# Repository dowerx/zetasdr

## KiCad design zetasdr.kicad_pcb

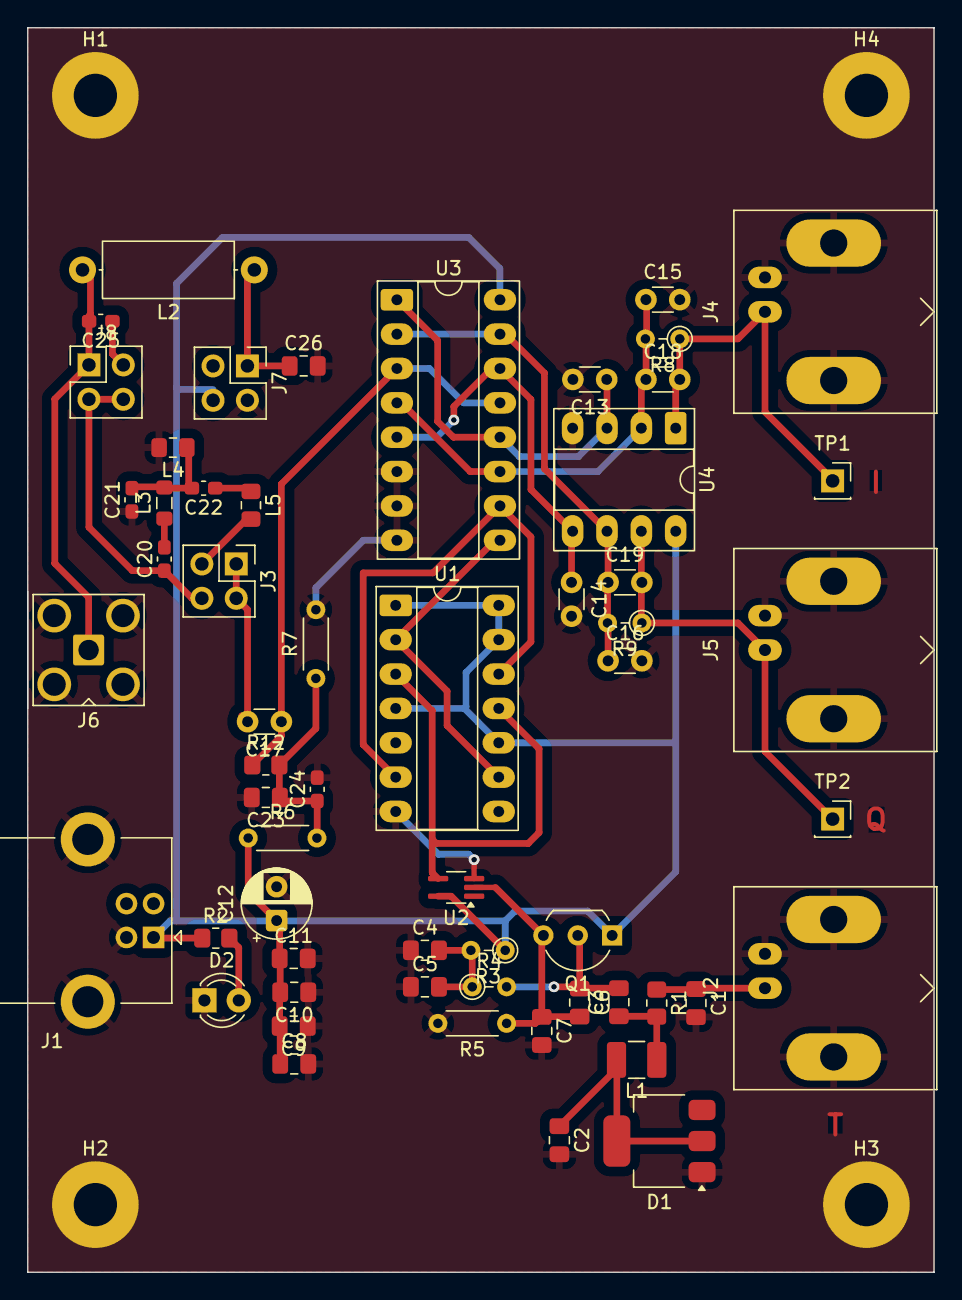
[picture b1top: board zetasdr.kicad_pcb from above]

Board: 2 copper layers, 67.0 x 92.0 mm, 62 parts (0 on the bottom side), 29 nets.

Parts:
C1, C3, C4, C8, C9, C10, C11, C23, C26: 100n; C_0805_2012Metric_Pad1.18x1.45mm_HandSolder
C2: DNP; C_0805_2012Metric_Pad1.18x1.45mm_HandSolder
C5: 1u; C_0805_2012Metric_Pad1.18x1.45mm_HandSolder
C6, C7: 82p; C_0805_2012Metric_Pad1.18x1.45mm_HandSolder
C12: 10u; CP_Radial_D5.0mm_P2.50mm
C13, C14, C15, C16: 22n; C_Disc_D3.0mm_W1.6mm_P2.50mm
C17: 1n; C_Disc_D3.0mm_W1.6mm_P2.50mm
C18, C19: 330p; C_Disc_D3.0mm_W1.6mm_P2.50mm
C20: 68p; C_0603_1608Metric_Pad1.08x0.95mm_HandSolder
C21, C24, C25: 10n; C_0603_1608Metric_Pad1.08x0.95mm_HandSolder
C22: 150p; C_0603_1608Metric_Pad1.08x0.95mm_HandSolder
D1: mv7404; SOT-223-3_TabPin2
D2: LED; LED_D3.0mm
H1, H2, H3, H4: MountingHole_Pad; MountingHole_3.2mm_M3_Pad
J1: USB_B; USB_B_Lumberg_2411_02_Horizontal
J2: Input AWG; BNC_Amphenol_B6252HB-NPP3G-50_Horizontal
J3, J7, J8: Conn_02x02_Counter_Clockwise; PinHeader_2x02_P2.54mm_Vertical
J4: Output I; BNC_Amphenol_B6252HB-NPP3G-50_Horizontal
J5: Output Q; BNC_Amphenol_B6252HB-NPP3G-50_Horizontal
J6: Antenna; SMA_Amphenol_901-143_Horizontal
L1: 4u7; L_1210_3225Metric_Pad1.42x2.65mm_HandSolder
L2: 22u; L_Axial_L9.5mm_D4.0mm_P12.70mm_Horizontal_Fastron_SMCC
L3: 27u; L_0805_2012Metric_Pad1.05x1.20mm_HandSolder
L4: 180n; L_0805_2012Metric_Pad1.15x1.40mm_HandSolder
L5: 12u; L_0805_2012Metric_Pad1.15x1.40mm_HandSolder
Q1: BC547C; TO-92_Inline_Wide
R1, R12: 100k; R_0805_2012Metric_Pad1.20x1.40mm_HandSolder
R2: 1k; R_0805_2012Metric_Pad1.20x1.40mm_HandSolder
R3, R4: 50k; R_Axial_DIN0204_L3.6mm_D1.6mm_P2.54mm_Vertical
R5: 380 (383); R_Axial_DIN0204_L3.6mm_D1.6mm_P5.08mm_Horizontal
R6, R7: 1k; R_Axial_DIN0204_L3.6mm_D1.6mm_P5.08mm_Horizontal
R8, R9: 5k1; R_Axial_DIN0204_L3.6mm_D1.6mm_P2.54mm_Vertical
TP1, TP2: TestPoint_Alt; PinSocket_1x01_P2.54mm_Vertical
U1: 74HC74; DIP-14_W7.62mm_Socket_LongPads
U2: 74AHC1G04; SOT-353_SC-70-5_Handsoldering
U3: 4052; DIP-16_W7.62mm_Socket_LongPads
U4: NE5532; DIP-8_W7.62mm_Socket_LongPads

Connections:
/80m szűrő/Input: C20.1, J3.4, J8.3, J8.4
/80m szűrő/Output: J3.3, L5.2
GND: C1.2, C2.2, C4.1, C5.1, C7.2, C8.2, C9.1, C10.1, C11.2, C12.2, C13.2, C14.2, C15.2, C16.2, C21.1, C23.2, C24.2, C26.2, D1.1 (A), D2.1 (K), H1.1, H2.1, H3.1, H4.1, J1.4 (GND), J1.5 (Shield), J2.2 (Ext), J4.2 (Ext), J5.2 (Ext), J6.2 (Ext), J7.2, L4.2, R5.2, R7.2, U1.7 (GND), U2.3 (GND), U3.6 (Inh), U3.7 (VEE), U3.8 (VSS), U4.4 (V-)
unnamed: C3.1, L1.1, R1.2
unnamed: C4.2, C5.2, R3.2, R4.1
unnamed: C20.2, L3.1
unnamed: C21.2, C22.2, L3.2, L4.1
unnamed: C22.1, L5.1
unnamed: C23.1, C24.1, R6.2, R7.1, R12.2
unnamed: C2.1, D1.2 (K), L1.2
unnamed: D2.2 (A), R2.2
unnamed: C1.1, J2.1 (In), R1.1
unnamed: C17.2, J3.1, J3.2
unnamed: C18.2, J4.1 (In), R8.1, TP1.1, U4.1
unnamed: C19.2, J5.1 (In), R9.1, TP2.1, U4.7
unnamed: C25.2, J6.1 (In), J8.1, L2.2
unnamed: C26.1, J7.1, L2.1
unnamed: C25.1, J8.2
unnamed: C3.2, C6.1, Q1.2 (B), R4.2
unnamed: C6.2, C7.1, Q1.3 (E), R5.1, U2.2
unnamed: U1.3 (C), U1.11 (C), U2.4
unnamed: U1.2 (D), U1.9 (Q), U3.9 (B)
unnamed: U1.6 (~Q), U1.12 (D), U3.10 (A)
unnamed: C13.1, U3.1 (Y0), U3.12 (X0), U4.3 (+)
unnamed: C14.1, U3.5 (Y1), U3.14 (X1), U4.5 (+)
unnamed: C16.1, C19.1, R9.2, U3.2 (Y2), U3.15 (X2), U4.6 (-)
unnamed: C15.1, C18.1, R8.2, U3.4 (Y3), U3.11 (X3), U4.2 (-)
unnamed: C17.1, R12.1, U3.3 (Y), U3.13 (X)
VCC: C8.1, C9.2, C10.2, C11.1, C12.1, J1.1 (VBUS), J7.4, Q1.1 (C), R2.1, R3.1, R6.1, U1.1 (~R), U1.4 (~S), U1.10 (~S), U1.13 (~R), U1.14 (VCC), U2.5 (VCC), U3.16 (VDD), U4.8 (V+)

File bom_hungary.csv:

"Reference","Qty","Value","DNP","Footprint","RET","Mouser"
"C1,C3,C4,C8,C9,C10,C11,C23,C26","9","100n","","Capacitor_SMD:C_0805_2012Metric_Pad1.18x1.45mm_HandSolder","CC0805KRX7R8BB104",""
"C2","1","DNP","DNP","Capacitor_SMD:C_0805_2012Metric_Pad1.18x1.45mm_HandSolder","-",""
"C5","1","1u","","Capacitor_SMD:C_0805_2012Metric_Pad1.18x1.45mm_HandSolder","-","963-MLASH21GBB5105KT "
"C6,C7","2","82p","","Capacitor_SMD:C_0805_2012Metric_Pad1.18x1.45mm_HandSolder","CC0805JRNPO9BN820",""
"C12","1","10u","","Capacitor_THT:CP_Radial_D5.0mm_P2.50mm","SE063M0010B2F-0511",""
"C13,C14,C15,C16","4","22n","","Capacitor_THT:C_Disc_D3.0mm_W1.6mm_P2.50mm","NCD223M50Z5U2.5MMLSF",""
"C17","1","1n","","Capacitor_THT:C_Disc_D3.0mm_W1.6mm_P2.50mm","NCD102K50Y5PTR2.5MMLSF",""
"C18,C19","2","330p","","Capacitor_THT:C_Disc_D3.0mm_W1.6mm_P2.50mm","NCD331K50Y5PTR2.5MMLSF",""
"C20","1","68p","","Capacitor_SMD:C_0603_1608Metric_Pad1.08x0.95mm_HandSolder","CC0603JRNPO9BN680",""
"C21,C24,C25","3","10n","","Capacitor_SMD:C_0603_1608Metric_Pad1.08x0.95mm_HandSolder","NMC0603X7R103K50TRPF",""
"C22","1","150p","","Capacitor_SMD:C_0603_1608Metric_Pad1.08x0.95mm_HandSolder","CC0603JRNPO9BN151",""
"D1","1","mv7404","","Package_TO_SOT_SMD:SOT-223-3_TabPin2","?",""
"D2","1","LED","","LED_THT:LED_D3.0mm","LTL-4221NLC",""
"H1,H2,H3,H4","4","MountingHole_Pad","","MountingHole:MountingHole_3.2mm_M3_Pad","-",""
"J1","1","USB_B","","Connector_USB:USB_B_Lumberg_2411_02_Horizontal"," UJ2-BH-W1-TH",""
"J2","1","Input AWG","","Connector_Coaxial:BNC_Amphenol_B6252HB-NPP3G-50_Horizontal","UG1094PR",""
"J3,J7,J8","3","Conn_02x02_Counter_Clockwise","","Connector_PinHeader_2.54mm:PinHeader_2x02_P2.54mm_Vertical","DIS-250-S037-55",""
"J4","1","Output I","","Connector_Coaxial:BNC_Amphenol_B6252HB-NPP3G-50_Horizontal","UG1094PR",""
"J5","1","Output Q","","Connector_Coaxial:BNC_Amphenol_B6252HB-NPP3G-50_Horizontal","UG1094PR",""
"J6","1","Antenna","","Connector_Coaxial:SMA_Amphenol_901-143_Horizontal","SMA6252A2-3GT50G-50",""
"L1","1","4u7","","Inductor_SMD:L_1210_3225Metric_Pad1.42x2.65mm_HandSolder","NLQ35M4R7TRF",""
"L2","1","22u","","Inductor_THT:L_Axial_L9.5mm_D4.0mm_P12.70mm_Horizontal_Fastron_SMCC","SMCC-220K-02",""
"L3","1","27u","","Inductor_SMD:L_0805_2012Metric_Pad1.05x1.20mm_HandSolder","-"," 652-CWF2012A-270K "
"L4","1","180n","","Inductor_SMD:L_0805_2012Metric_Pad1.15x1.40mm_HandSolder","-","652-CWF1612A-R18K "
"L5","1","12u","","Inductor_SMD:L_0805_2012Metric_Pad1.15x1.40mm_HandSolder","-"," 652-CWF2012A-120K "
"Q1","1","BC547C","","Package_TO_SOT_THT:TO-92_Inline_Wide","BC547CBK",""
"R1,R12","2","100k","","Resistor_SMD:R_0805_2012Metric_Pad1.20x1.40mm_HandSolder","RC0805FR-07100KL",""
"R2","1","1k","","Resistor_SMD:R_0805_2012Metric_Pad1.20x1.40mm_HandSolder","RC0805JR-071KL",""
"R3,R4","2","50k","","Resistor_THT:R_Axial_DIN0204_L3.6mm_D1.6mm_P2.54mm_Vertical","MF0207FTE52-51K",""
"R5","1","380 (383)","","Resistor_THT:R_Axial_DIN0204_L3.6mm_D1.6mm_P5.08mm_Horizontal","-","279-LR1F383R"
"R6,R7","2","1k","","Resistor_THT:R_Axial_DIN0204_L3.6mm_D1.6mm_P5.08mm_Horizontal","CFR-25JT-52-1K",""
"R8,R9","2","5k1","","Resistor_THT:R_Axial_DIN0204_L3.6mm_D1.6mm_P2.54mm_Vertical","CFR-25JT-52-5K1",""
"TP1,TP2","2","TestPoint_Alt","","Connector_PinSocket_2.54mm:PinSocket_1x01_P2.54mm_Vertical","",""
"U1","1","74HC74","","Package_DIP:DIP-14_W7.62mm_Socket_LongPads","CD74HC74E",""
"U2","1","74AHC1G04","","Package_TO_SOT_SMD:SOT-353_SC-70-5_Handsoldering","-","621-74AHC1G04SE-7 "
"U3","1","4052","","Package_DIP:DIP-16_W7.62mm_Socket_LongPads","-","595-CD4052BEE4 "
"U4","1","NE5532","","Package_DIP:DIP-8_W7.62mm_Socket_LongPads","NE5532AP",""

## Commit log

2025-09-07 add connectors for picoscope
2025-09-07 first layout
2025-09-14 80m filter & new layout
2025-09-28 rf bias filtering
2025-09-29 bias tee
2025-10-02 bias tee power filter
